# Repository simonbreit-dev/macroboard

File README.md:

# Makroboard

A macropad with twelve keys, two rotary encoders with push buttons, twelve
addressable RGB LEDs, and an RP2040. The 80 × 82 mm PCB uses four copper layers
and has a USB-C connector on its top edge.

This repository contains the editable electronics design. Firmware, an app, and
an enclosure are not included yet. The design **has not been tested as a physical
prototype**; USB communication, power supplies, and controls must be verified on
an assembled board.

## Getting started

1. Install KiCad 10, including its standard libraries. The design was edited with
   KiCad 10.0.7.
2. Open [`electronics/makroboard.kicad_pro`](electronics/makroboard.kicad_pro).
3. Read the [electronics documentation](electronics/README.md) and, before
   manufacturing, the [fabrication requirements](electronics/FABRICATION-NOTES.txt).

Project-specific symbols and footprints are included. The optional 3D models for
the USB-C connector and encoders are not included in the published project; all
pads, holes, and electrical connections are included.

## Files and exports

- `electronics/`: KiCad project, schematics, PCB, and library tables.
- `electronics/lib/footprints/`: local footprints used by the PCB.
- `LICENSE`, `LICENSES/`, `THIRD_PARTY.md`: license texts, attribution, and
  licensing notes.

Gerbers, drill files, assembly exports, previews, check results, and local agent
files are not versioned. Existing local files remain excluded by `.gitignore`.
Manufacturing files are exported from KiCad for the relevant revision; commands
are provided in the electronics documentation.

## Contributing

See [CONTRIBUTING.md](CONTRIBUTING.md). Keep hardware changes and documentation
consistent, and preserve the license notices.

## License and attribution

Copyright © 2026 Simon Breit. Original hardware contributions and the associated
project documentation are licensed under **CERN-OHL-P-2.0**; the full text is in
[LICENSE](LICENSE).

Third-party material retains its respective terms. The Raspberry Pi reference
design is licensed under MIT, KiCad library material under CC-BY-SA-4.0 with the
KiCad exception, and marbastlib key footprints under CERN-OHL-P-2.0.
The encoder footprints match those from
[ubiqueIoT/rotary-encoder-PEC11R](https://github.com/ubiqueIoT/rotary-encoder-PEC11R).
See [THIRD_PARTY.md](THIRD_PARTY.md) for further attribution and licensing notes.
CERN-OHL-P-2.0 does not grant additional rights to this third-party material.

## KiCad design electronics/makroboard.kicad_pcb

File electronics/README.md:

# Electronics

Revision **TOP-USB**, 2026-10-17: 80 × 82 mm, four copper layers, nominal finished
PCB thickness of 1.0 mm. Twelve keys form a 4×3 matrix with 19.05 mm key spacing;
the top row is 23 mm from the lower 3×3 block. Two encoders with push buttons sit
at the lower right, with USB-C on the top edge.

## Opening the project

Open `makroboard.kicad_pro` with KiCad 10. The files were edited with KiCad 10.0.7.
The KiCad standard libraries are required, along with the included
`Makroboard.kicad_sym` symbol library and the footprints under
`lib/footprints/Makroboard_PCB.pretty/`. The library tables use project-relative
paths.

`makroboard.kicad_sch` is the main schematic;
`RPI-RP2040-MINIMAL_R3-S1.kicad_sch` is the required controller subsheet, adapted
for Makroboard. Its filename identifies the original reference design. See
[THIRD_PARTY.md](../THIRD_PARTY.md) for attribution and licenses.

The optional external 3D models for USB-C and the encoders are not included.
Other components use embedded reference models and KiCad standard models.
Enclosure and control dimensions must be checked against manufacturer data;
no enclosure design is included.

## Assembly and fabrication

67 SMD/hybrid components are on Bottom; the two required 100 nF capacitors C20/C21
are on Top. C20/C21 use 0805 packages and can be hand-soldered after single-sided
factory assembly. One suitable part is Yageo CC0805KRX7R9BB104, LCSC C49678,
100 nF, 50 V, X7R, 10%.

R3 remains DNP. Keys, encoders, and the optional BOOT header J2 are assembled
separately. Test pads are not purchased components. The LEDs are reverse-mount
SK6812MINI-E devices on Bottom, shining through the PCB toward Top; confirm the
exact variant, pinout, and permitted brightness against the datasheet.

Include the [fabrication requirements](FABRICATION-NOTES.txt) with every
manufacturing order. In particular, the manufacturer must confirm 90 Ω ±10% USB
differential impedance for its actual four-layer stackup.

## Firmware interface

Firmware and an app are not included. The following assignments describe the
current design; they are not instructions for firmware that is already available.

| Signal | GPIO | RP2040 pin |
|---|---:|---:|
| MATRIX_COL_1 | 0 | 2 |
| MATRIX_COL_2 | 18 | 29 |
| MATRIX_COL_3 | 17 | 28 |
| MATRIX_ROW_1 | 3 | 5 |
| MATRIX_ROW_2 | 22 | 34 |
| MATRIX_ROW_3 | 11 | 14 |
| MATRIX_ROW_4 | 6 | 8 |
| LED_DATA | 8 | 11 |
| ENC_1_A | 29 | 41 |
| ENC_1_B | 28 | 40 |
| ENC_1_PUSH | 9 | 12 |
| ENC_2_A | 26 | 38 |
| ENC_2_B | 19 | 30 |
| ENC_2_PUSH | 24 | 36 |

The LED chain starts below SW3 at the upper right and follows a serpentine path
down the board:

| LED index (zero-based) | LED | Key | Matrix row | Matrix column |
|---:|---|---|---:|---:|
| 0 | D1 | SW3 | 1 | 3 |
| 1 | D2 | SW2 | 1 | 2 |
| 2 | D3 | SW1 | 1 | 1 |
| 3 | D4 | SW4 | 2 | 1 |
| 4 | D5 | SW5 | 2 | 2 |
| 5 | D6 | SW6 | 2 | 3 |
| 6 | D7 | SW9 | 3 | 3 |
| 7 | D8 | SW8 | 3 | 2 |
| 8 | D9 | SW7 | 3 | 1 |
| 9 | D10 | SW10 | 4 | 1 |
| 10 | D11 | SW11 | 4 | 2 |
| 11 | D12 | SW12 | 4 | 3 |

## Checks and exports

Run these commands from the repository root. On macOS, add
`/Applications/KiCad/KiCad.app/Contents/MacOS/` to `PATH` to use `kicad-cli`.
Outputs remain local and are excluded by `.gitignore`.

```sh
mkdir -p electronics/checks electronics/generated/gerbers
kicad-cli sch erc --format json --severity-all --exit-code-violations \
  -o electronics/checks/erc.json electronics/makroboard.kicad_sch
kicad-cli pcb drc --format json --schematic-parity --refill-zones \
  --exit-code-violations -o electronics/checks/drc.json \
  electronics/makroboard.kicad_pcb
kicad-cli pcb export gerbers \
  --layers F.Cu,In1.Cu,In2.Cu,B.Cu,F.Mask,B.Mask,F.Silkscreen,B.Silkscreen,F.Paste,B.Paste,Edge.Cuts \
  --use-drill-file-origin --subtract-soldermask --check-zones \
  -o electronics/generated/gerbers/ electronics/makroboard.kicad_pcb
kicad-cli pcb export drill --format excellon --drill-origin plot \
  --excellon-separate-th --excellon-oval-format route \
  -o electronics/generated/gerbers/ electronics/makroboard.kicad_pcb
```

Always generate Gerbers, drill files, and any BOM/placement files from the same
project revision, and inspect them together in KiCad/Gerber Viewer. For new
assembly exports, explicitly define which parts are factory-assembled and which
are hand-soldered. The assembler must verify machine rotation offsets against
the pin-1 markings. Old local exports are not an approved manufacturing package.

The project intentionally disables some ERC/DRC rules, such as missing
courtyards. Interpret a successful check within that configuration; it does not
verify enclosure fit or hardware functionality.

## First power-up

The design **has not been tested as a physical prototype**. After completing
assembly, including C20/C21, check for solder bridges, monitor current draw, and
verify the +3V3 and +1V1 supplies.

To enter the ROM USB bootloader, connect J2 pin 1 to GND, briefly pull RUN at TP3
to GND and release it, then release BOOT. `RPI-RP2` should appear. Alternatively,
use TP1 SWCLK, TP2 SWDIO, TP3 RUN, TP4 GND, and TP5 as the 3.3 V reference for SWD.
Start LED testing at low brightness. Power-up, flashing, USB communication, and
key/encoder/LED operation must be verified on an assembled board with suitable
firmware.

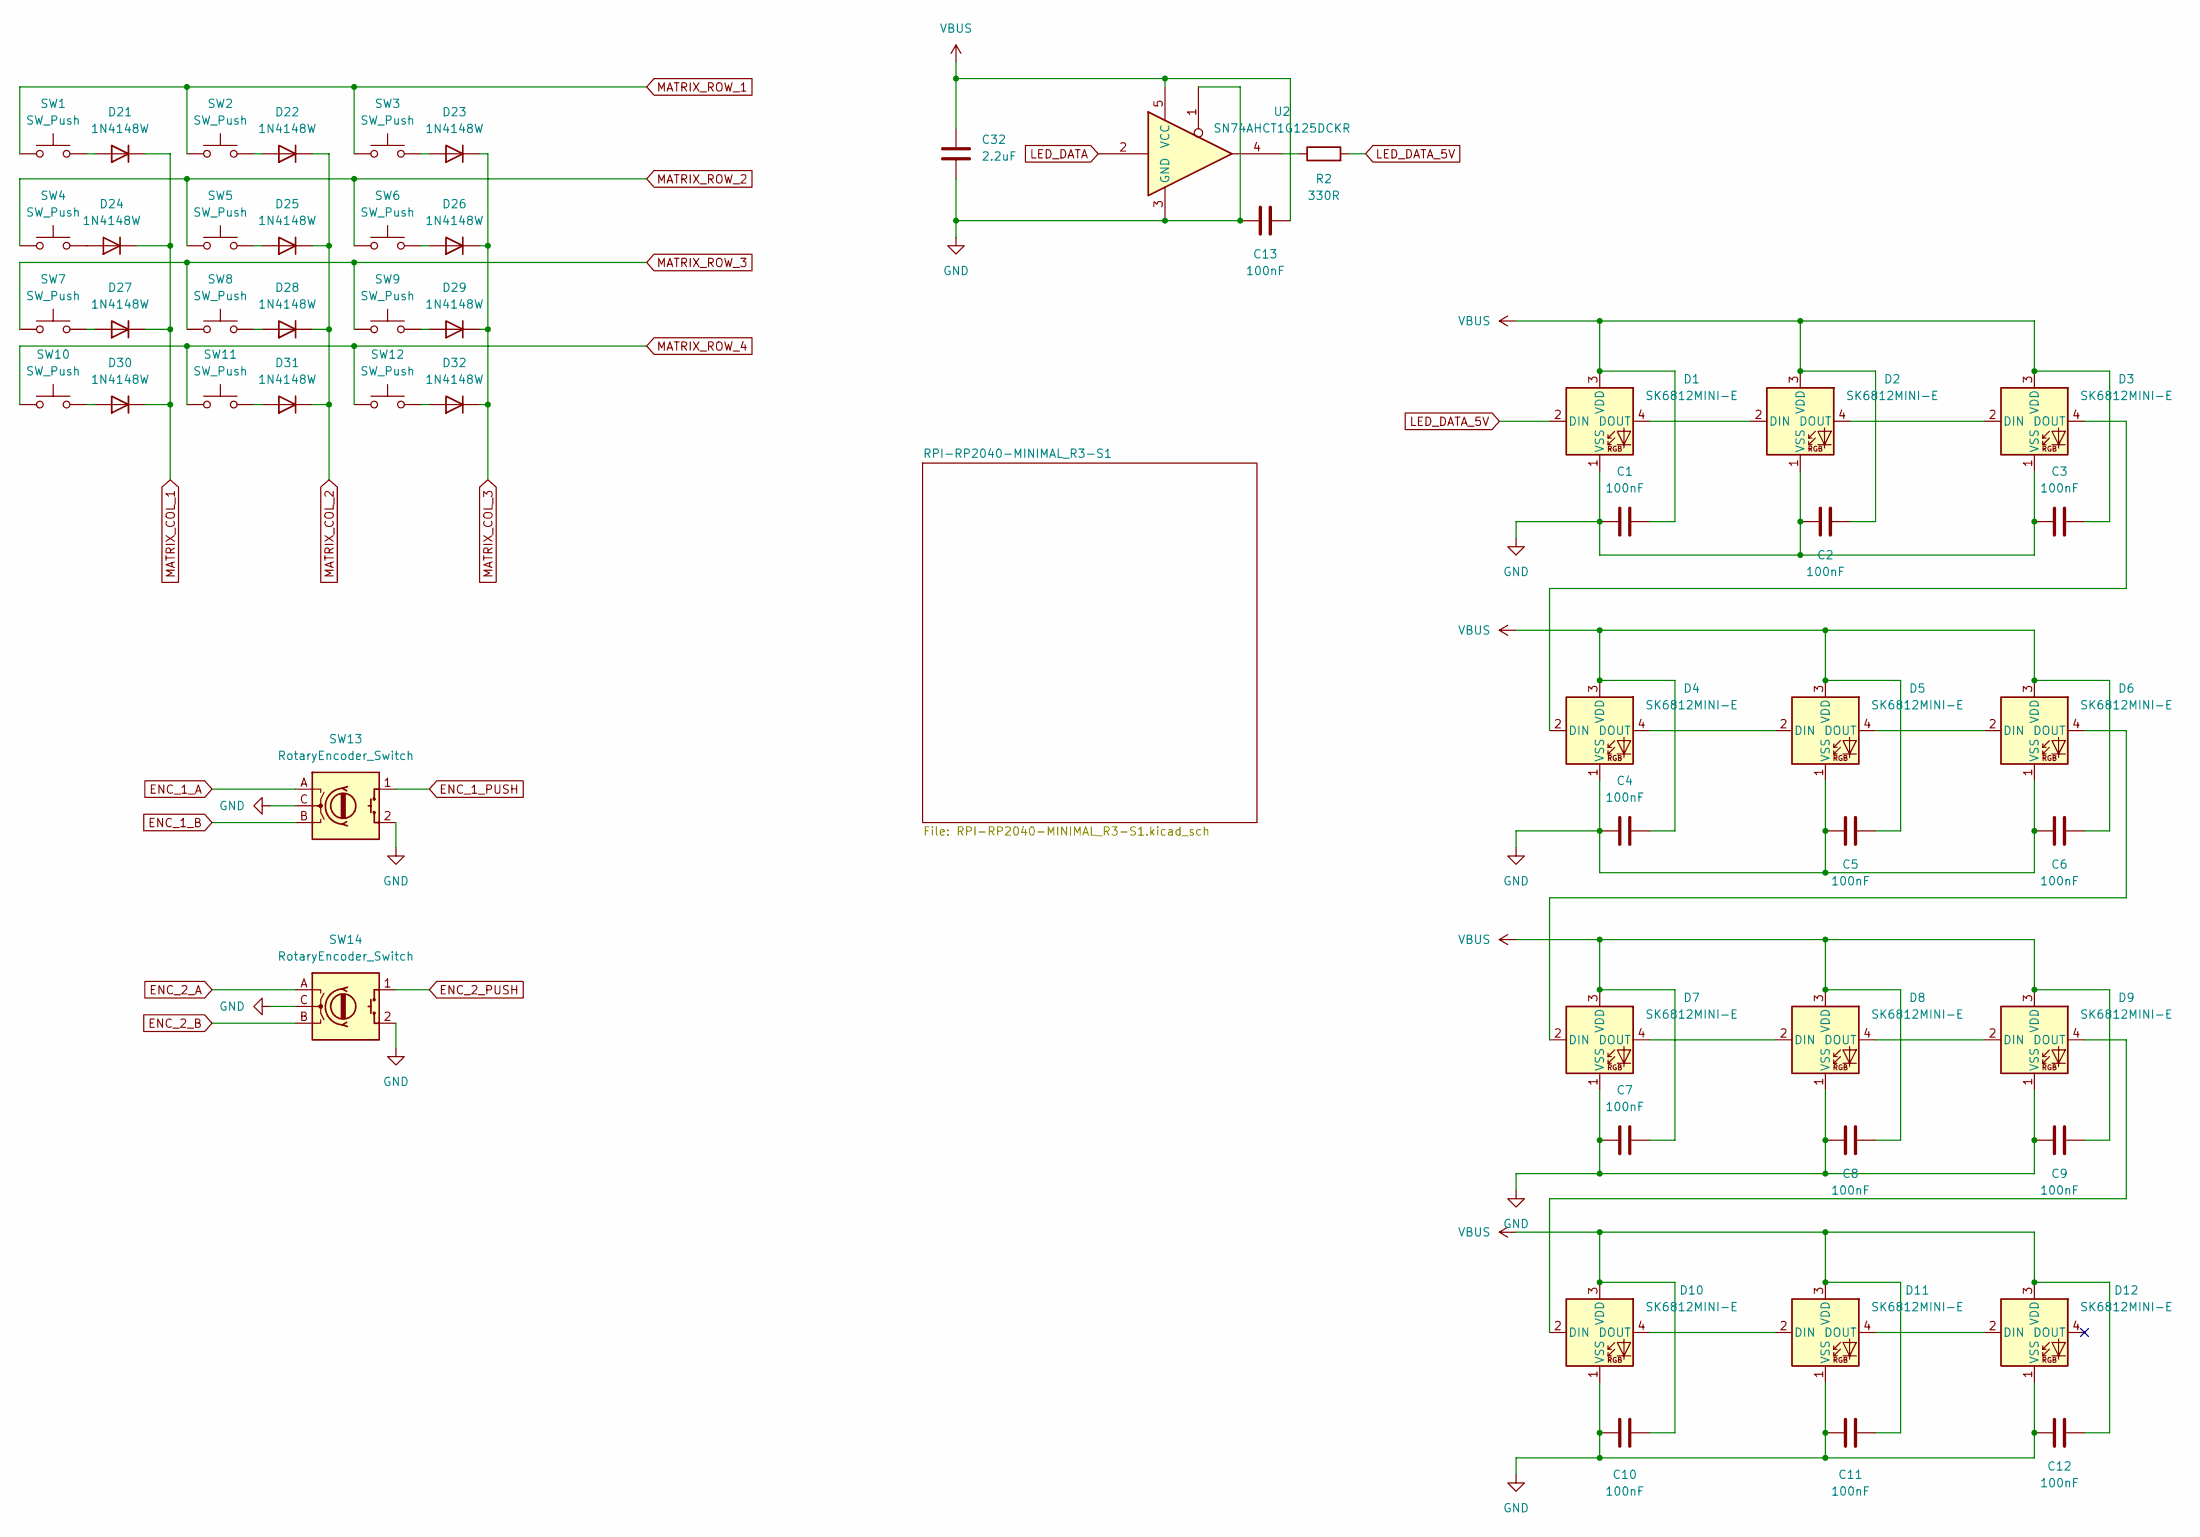
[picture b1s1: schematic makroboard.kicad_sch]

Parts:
C1: 100nF; C1_C_0805_2012Metric; manufacturer_pn CC0805KRX7R9BB104; LCSC C49678
C2: 100nF; C2_C_0805_2012Metric; manufacturer_pn CC0805KRX7R9BB104; LCSC C49678
C3: 100nF; C3_C_0805_2012Metric; manufacturer_pn CC0805KRX7R9BB104; LCSC C49678
C4: 100nF; C4_C_0805_2012Metric; manufacturer_pn CC0805KRX7R9BB104; LCSC C49678
C5: 100nF; C5_C_0805_2012Metric; manufacturer_pn CC0805KRX7R9BB104; LCSC C49678
C6: 100nF; C6_C_0805_2012Metric; manufacturer_pn CC0805KRX7R9BB104; LCSC C49678
C7: 100nF; C7_C_0805_2012Metric; manufacturer_pn CC0805KRX7R9BB104; LCSC C49678
C8: 100nF; C8_C_0805_2012Metric; manufacturer_pn CC0805KRX7R9BB104; LCSC C49678
C9: 100nF; C9_C_0805_2012Metric; manufacturer_pn CC0805KRX7R9BB104; LCSC C49678
C10: 100nF; C10_C_0805_2012Metric; manufacturer_pn CC0805KRX7R9BB104; LCSC C49678
C11: 100nF; C11_C_0805_2012Metric; manufacturer_pn CC0805KRX7R9BB104; LCSC C49678
C12: 100nF; C12_C_0805_2012Metric; manufacturer_pn CC0805KRX7R9BB104; LCSC C49678
C13: 100nF; C13_C_0805_2012Metric; manufacturer_pn CC0805KRX7R9BB104; LCSC C49678
C32: 2.2uF; C32_C_0805_2012Metric; manufacturer_pn CL21B225KOFNNNE; LCSC C28234
D1: SK6812MINI-E; D1_LED_SK6812MINI-E_3.2x2.8mm_P1.5mm_ReverseMount; manufacturer_pn SK6812MINI-E; LCSC C5149201
D2: SK6812MINI-E; D2_LED_SK6812MINI-E_3.2x2.8mm_P1.5mm_ReverseMount; manufacturer_pn SK6812MINI-E; LCSC C5149201
D3: SK6812MINI-E; D3_LED_SK6812MINI-E_3.2x2.8mm_P1.5mm_ReverseMount; manufacturer_pn SK6812MINI-E; LCSC C5149201
D4: SK6812MINI-E; D4_LED_SK6812MINI-E_3.2x2.8mm_P1.5mm_ReverseMount; manufacturer_pn SK6812MINI-E; LCSC C5149201
D5: SK6812MINI-E; D5_LED_SK6812MINI-E_3.2x2.8mm_P1.5mm_ReverseMount; manufacturer_pn SK6812MINI-E; LCSC C5149201
D6: SK6812MINI-E; D6_LED_SK6812MINI-E_3.2x2.8mm_P1.5mm_ReverseMount; manufacturer_pn SK6812MINI-E; LCSC C5149201
D7: SK6812MINI-E; D7_LED_SK6812MINI-E_3.2x2.8mm_P1.5mm_ReverseMount; manufacturer_pn SK6812MINI-E; LCSC C5149201
D8: SK6812MINI-E; D8_LED_SK6812MINI-E_3.2x2.8mm_P1.5mm_ReverseMount; manufacturer_pn SK6812MINI-E; LCSC C5149201
D9: SK6812MINI-E; D9_LED_SK6812MINI-E_3.2x2.8mm_P1.5mm_ReverseMount; manufacturer_pn SK6812MINI-E; LCSC C5149201
D10: SK6812MINI-E; D10_LED_SK6812MINI-E_3.2x2.8mm_P1.5mm_ReverseMount; manufacturer_pn SK6812MINI-E; LCSC C5149201
D11: SK6812MINI-E; D11_LED_SK6812MINI-E_3.2x2.8mm_P1.5mm_ReverseMount; manufacturer_pn SK6812MINI-E; LCSC C5149201
D12: SK6812MINI-E; D12_LED_SK6812MINI-E_3.2x2.8mm_P1.5mm_ReverseMount; manufacturer_pn SK6812MINI-E; LCSC C5149201
D21: 1N4148W; D21_D_SOD-123; manufacturer_pn 1N4148W; LCSC C81598
D22: 1N4148W; D22_D_SOD-123; manufacturer_pn 1N4148W; LCSC C81598
D23: 1N4148W; D23_D_SOD-123; manufacturer_pn 1N4148W; LCSC C81598
D24: 1N4148W; D24_D_SOD-123; manufacturer_pn 1N4148W; LCSC C81598
D25: 1N4148W; D25_D_SOD-123; manufacturer_pn 1N4148W; LCSC C81598
D26: 1N4148W; D26_D_SOD-123; manufacturer_pn 1N4148W; LCSC C81598
D27: 1N4148W; D27_D_SOD-123; manufacturer_pn 1N4148W; LCSC C81598
D28: 1N4148W; D28_D_SOD-123; manufacturer_pn 1N4148W; LCSC C81598
D29: 1N4148W; D29_D_SOD-123; manufacturer_pn 1N4148W; LCSC C81598
D30: 1N4148W; D30_D_SOD-123; manufacturer_pn 1N4148W; LCSC C81598
D31: 1N4148W; D31_D_SOD-123; manufacturer_pn 1N4148W; LCSC C81598
D32: 1N4148W; D32_D_SOD-123; manufacturer_pn 1N4148W; LCSC C81598
R2: 330R; R2_R_0805_2012Metric; manufacturer_pn 0805W8F3300T5E; LCSC C17630
SW1: SW_Push; SW1_SW_choc_v2_1u
SW2: SW_Push; SW2_SW_choc_v2_1u
SW3: SW_Push; SW3_SW_choc_v2_1u
SW4: SW_Push; SW4_SW_choc_v2_1u
SW5: SW_Push; SW5_SW_choc_v2_1u
SW6: SW_Push; SW6_SW_choc_v2_1u
SW7: SW_Push; SW7_SW_choc_v2_1u
SW8: SW_Push; SW8_SW_choc_v2_1u
SW9: SW_Push; SW9_SW_choc_v2_1u
SW10: SW_Push; SW10_SW_choc_v2_1u
SW11: SW_Push; SW11_SW_choc_v2_1u
SW12: SW_Push; SW12_SW_choc_v2_1u
SW13: RotaryEncoder_Switch; SW13_Bourns-PEC11R-4220F-S0024-0-0-0
SW14: RotaryEncoder_Switch; SW14_Bourns-PEC11R-4220F-S0024-0-0-0
U2: SN74AHCT1G125DCKR; U2_SOT-353_SC-70-5; manufacturer_pn SN74AHCT1G125DCKR; LCSC C350557

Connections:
ENC_1_A: SW13.A; also elsewhere on the board
ENC_1_B: SW13.B; also elsewhere on the board
ENC_1_PUSH: SW13.1 (S1); also elsewhere on the board
ENC_2_A: SW14.A; also elsewhere on the board
ENC_2_B: SW14.B; also elsewhere on the board
ENC_2_PUSH: SW14.1 (S1); also elsewhere on the board
GND: C1.2, C2.2, C3.2, C4.2, C5.2, C6.2, C7.2, C8.2, C9.2, C10.2, C11.2, C12.2, C13.2, C32.2, D1.1 (VSS), D2.1 (VSS), D3.1 (VSS), D4.1 (VSS), D5.1 (VSS), D6.1 (VSS), D7.1 (VSS), D8.1 (VSS), D9.1 (VSS), D10.1 (VSS), D11.1 (VSS), D12.1 (VSS), SW13.2 (S2), SW13.C, SW14.2 (S2), SW14.C, U2.1, U2.3 (GND); also elsewhere on the board
LED_DATA: U2.2; also elsewhere on the board
LED_DATA_5V: D1.2 (DIN), R2.2
MATRIX_COL_1: D21.1 (K), D24.1 (K), D27.1 (K), D30.1 (K); also elsewhere on the board
MATRIX_COL_2: D22.1 (K), D25.1 (K), D28.1 (K), D31.1 (K); also elsewhere on the board
MATRIX_COL_3: D23.1 (K), D26.1 (K), D29.1 (K), D32.1 (K); also elsewhere on the board
MATRIX_ROW_1: SW1.1, SW2.1, SW3.1; also elsewhere on the board
MATRIX_ROW_2: SW4.1, SW5.1, SW6.1; also elsewhere on the board
MATRIX_ROW_3: SW7.1, SW8.1, SW9.1; also elsewhere on the board
MATRIX_ROW_4: SW10.1, SW11.1, SW12.1; also elsewhere on the board
unnamed: D1.4 (DOUT), D2.2 (DIN)
unnamed: D2.4 (DOUT), D3.2 (DIN)
unnamed: D3.4 (DOUT), D4.2 (DIN)
unnamed: D4.4 (DOUT), D5.2 (DIN)
unnamed: D5.4 (DOUT), D6.2 (DIN)
unnamed: D6.4 (DOUT), D7.2 (DIN)
unnamed: D7.4 (DOUT), D8.2 (DIN)
unnamed: D8.4 (DOUT), D9.2 (DIN)
unnamed: D9.4 (DOUT), D10.2 (DIN)
unnamed: D10.4 (DOUT), D11.2 (DIN)
unnamed: D11.4 (DOUT), D12.2 (DIN)
unnamed: D21.2 (A), SW1.2
unnamed: D22.2 (A), SW2.2
unnamed: D23.2 (A), SW3.2
unnamed: D24.2 (A), SW4.2
unnamed: D25.2 (A), SW5.2
unnamed: D26.2 (A), SW6.2
unnamed: D27.2 (A), SW7.2
unnamed: D28.2 (A), SW8.2
unnamed: D29.2 (A), SW9.2
unnamed: D30.2 (A), SW10.2
unnamed: D31.2 (A), SW11.2
unnamed: D32.2 (A), SW12.2
unnamed: R2.1, U2.4
VBUS: C1.1, C2.1, C3.1, C4.1, C5.1, C6.1, C7.1, C8.1, C9.1, C10.1, C11.1, C12.1, C13.1, C32.1, D1.3 (VDD), D2.3 (VDD), D3.3 (VDD), D4.3 (VDD), D5.3 (VDD), D6.3 (VDD), D7.3 (VDD), D8.3 (VDD), D9.3 (VDD), D10.3 (VDD), D11.3 (VDD), D12.3 (VDD), U2.5 (VCC); also elsewhere on the board

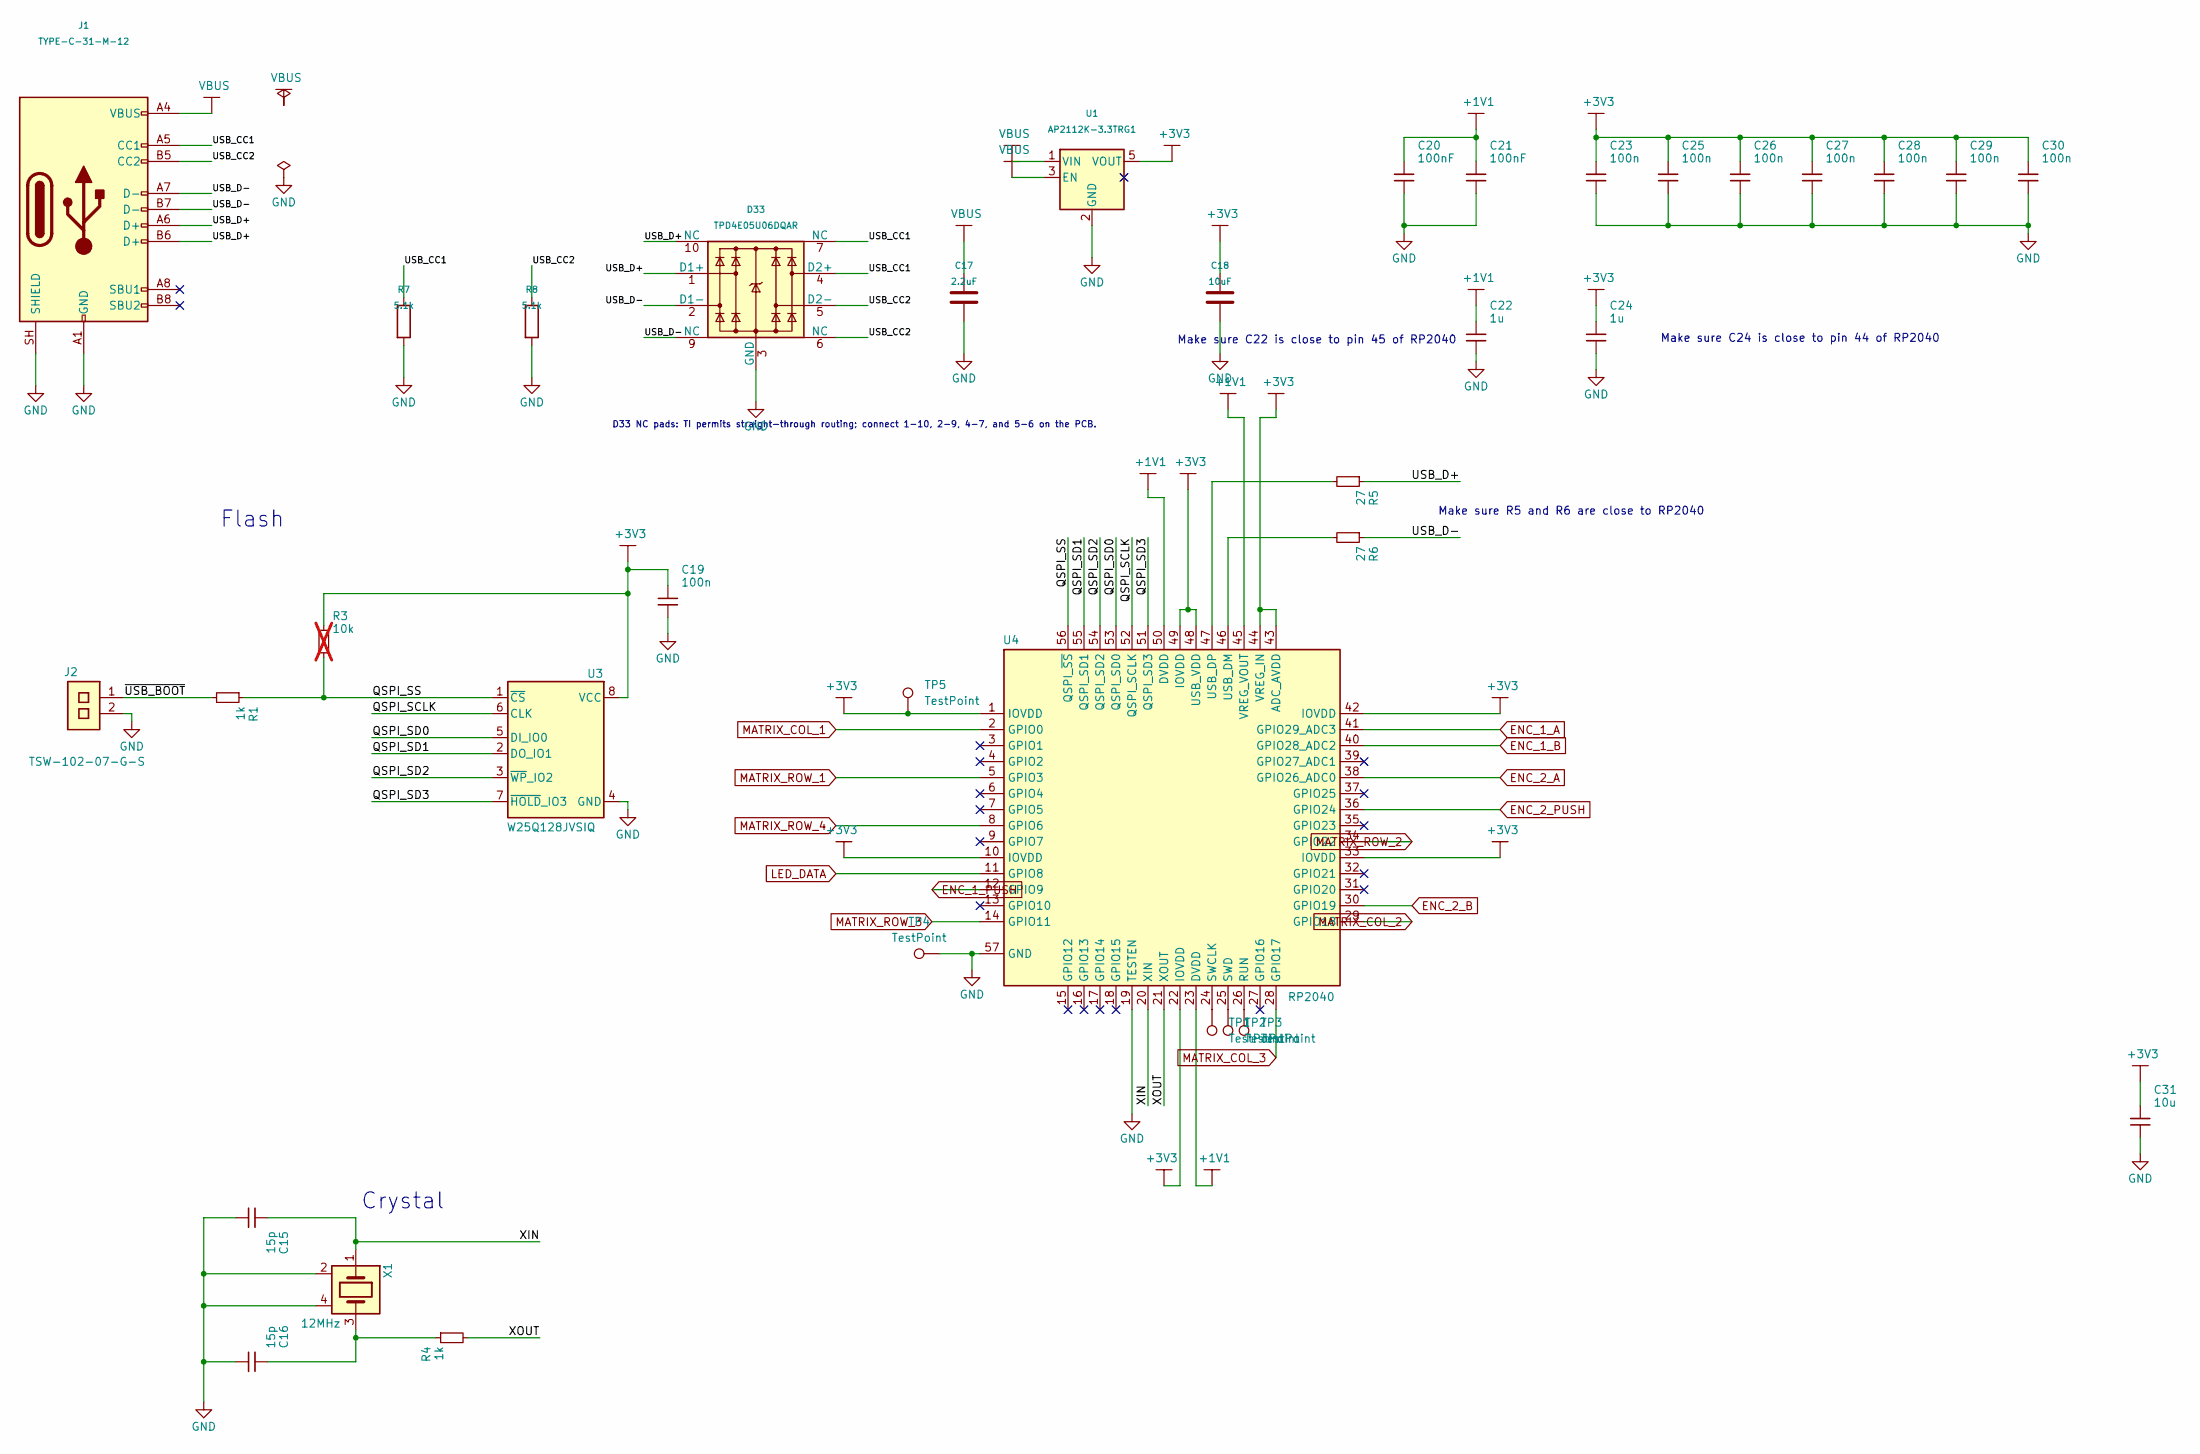
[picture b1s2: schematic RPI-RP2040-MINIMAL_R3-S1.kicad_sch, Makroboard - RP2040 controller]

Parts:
C15: 15p; C15_generic_capc1005x50; manufacturer_pn 0402CG150J500NT; LCSC C1548
C16: 15p; C16_generic_capc1005x50; manufacturer_pn 0402CG150J500NT; LCSC C1548
C17: 2.2uF; C17_generic_capc2012x125; manufacturer_pn CL21B225KOFNNNE; LCSC C28234
C18: 10uF; C18_generic_capc2012x125; manufacturer_pn CL21A106KAYNNNE; LCSC C15850
C19: 100n; C19_generic_capc1005x50; manufacturer_pn CL05B104KO5NNNC; LCSC C1525
C20: 100nF; C20_C_0805_2012Metric; manufacturer_pn CC0805KRX7R9BB104; LCSC C49678
C21: 100nF; C21_C_0805_2012Metric; manufacturer_pn CC0805KRX7R9BB104; LCSC C49678
C22: 1u; C22_generic_capc1005x50; manufacturer_pn CL05A105KA5NQNC; LCSC C52923
C23: 100n; C23_generic_capc1005x50; manufacturer_pn CL05B104KO5NNNC; LCSC C1525
C24: 1u; C24_generic_capc1005x50; manufacturer_pn CL05A105KA5NQNC; LCSC C52923
C25: 100n; C25_generic_capc1005x50; manufacturer_pn CL05B104KO5NNNC; LCSC C1525
C26: 100n; C26_generic_capc1005x50; manufacturer_pn CL05B104KO5NNNC; LCSC C1525
C27: 100n; C27_generic_capc1005x50; manufacturer_pn CL05B104KO5NNNC; LCSC C1525
C28: 100n; C28_generic_capc1005x50; manufacturer_pn CL05B104KO5NNNC; LCSC C1525
C29: 100n; C29_generic_capc1005x50; manufacturer_pn CL05B104KO5NNNC; LCSC C1525
C30: 100n; C30_generic_capc1005x50; manufacturer_pn CL05B104KO5NNNC; LCSC C1525
C31: 10u; C31_generic_capc2012x125; manufacturer_pn CL21A106KAYNNNE; LCSC C15850
D33: TPD4E05U06DQAR; D33_USON-10_2.5x1.0mm_P0.5mm; manufacturer_pn TPD4E05U06DQAR; LCSC C138714
J1: TYPE-C-31-M-12; J1_USB_C_Receptacle_HRO_TYPE-C-31-M-12; manufacturer_pn TYPE-C-31-M-12; LCSC C165948
J2: TSW-102-07-G-S; J2_samtec_tsw-102-07-g-s; part_uid RP-01JV5X-LY21H5
R1: 1k; R1_generic_resc1005x35; manufacturer_pn 0402WGF1001TCE; LCSC C11702
R3: 10k; R3_generic_resc1005x35; manufacturer_pn 0402WGF1002TCE; LCSC C25744; not fitted
R4: 1k; R4_generic_resc1005x35; manufacturer_pn 0402WGF1001TCE; LCSC C11702
R5: 27; R5_generic_resc1005x35; manufacturer_pn 0402WGF270JTCE; LCSC C25100
R6: 27; R6_generic_resc1005x35; manufacturer_pn 0402WGF270JTCE; LCSC C25100
R7: 5.1k; R7_R_0603_1608Metric; manufacturer_pn 0603WAF5101T5E; LCSC C23186
R8: 5.1k; R8_R_0603_1608Metric; manufacturer_pn 0603WAF5101T5E; LCSC C23186
TP1: TestPoint; TP1_TestPoint_Pad_D1.5mm
TP2: TestPoint; TP2_TestPoint_Pad_D1.5mm
TP3: TestPoint; TP3_TestPoint_Pad_D1.5mm
TP4: TestPoint; TP4_TestPoint_Pad_D1.5mm
TP5: TestPoint; TP5_TestPoint_Pad_D1.5mm
U1: AP2112K-3.3TRG1; U1_SOT-23-5; manufacturer_pn AP2112K-3.3TRG1; LCSC C51118
U3: W25Q128JVSIQ; U3_generic_soic127p790x195-8; manufacturer_pn W25Q128JVSIQ; LCSC C97521
U4: RP2040; U4_rpi_rp2040_vias; manufacturer_pn RP2040; LCSC C2040
X1: 12MHz; X1_generic_xtalcc320x250x80-4; manufacturer_pn ABM8-272-T3; LCSC C20625731

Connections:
+1V1: C20.1, C21.1, C22.1, U4.23 (DVDD), U4.45 (VREG_VOUT), U4.50 (DVDD)
+3V3: C18.1, C19.1, C23.1, C24.1, C25.1, C26.1, C27.1, C28.1, C29.1, C30.1, C31.1, R3.1, TP5.1 (1_1), U1.5 (VOUT), U3.8 (VCC), U4.1 (IOVDD), U4.10 (IOVDD), U4.22 (IOVDD), U4.33 (IOVDD), U4.42 (IOVDD), U4.43 (ADC_AVDD), U4.44 (VREG_IN), U4.48 (USB_VDD), U4.49 (IOVDD)
/RPI-RP2040-MINIMAL_R3-S1/QSPI_SCLK: U3.6 (CLK), U4.52 (QSPI_SCLK)
/RPI-RP2040-MINIMAL_R3-S1/QSPI_SD0: U3.5 (DI_IO0), U4.53 (QSPI_SD0)
/RPI-RP2040-MINIMAL_R3-S1/QSPI_SD1: U3.2 (DO_IO1), U4.55 (QSPI_SD1)
/RPI-RP2040-MINIMAL_R3-S1/QSPI_SD2: U3.3 (~WP_IO2), U4.54 (QSPI_SD2)
/RPI-RP2040-MINIMAL_R3-S1/QSPI_SD3: U3.7 (~HOLD_IO3), U4.51 (QSPI_SD3)
/RPI-RP2040-MINIMAL_R3-S1/QSPI_SS: R1.1, R3.2, U3.1 (~CS), U4.56 (QSPI_~SS)
/RPI-RP2040-MINIMAL_R3-S1/USB_CC1: D33.4 (D2+), D33.7 (NC), J1.A5 (CC1), R7.1
/RPI-RP2040-MINIMAL_R3-S1/USB_CC2: D33.5 (D2-), D33.6 (NC), J1.B5 (CC2), R8.1
/RPI-RP2040-MINIMAL_R3-S1/USB_D+: D33.1 (D1+), D33.10 (NC), J1.A6 (D+), J1.B6 (D+), R5.1
/RPI-RP2040-MINIMAL_R3-S1/USB_D-: D33.2 (D1-), D33.9 (NC), J1.A7 (D-), J1.B7 (D-), R6.1
/RPI-RP2040-MINIMAL_R3-S1/XIN: C15.1, U4.20 (XIN), X1.1
/RPI-RP2040-MINIMAL_R3-S1/XOUT: R4.2, U4.21 (XOUT)
/RPI-RP2040-MINIMAL_R3-S1/~USB_BOOT: J2.1, R1.2
ENC_1_A: U4.41 (GPIO29_ADC3); also elsewhere on the board
ENC_1_B: U4.40 (GPIO28_ADC2); also elsewhere on the board
ENC_1_PUSH: U4.12 (GPIO9); also elsewhere on the board
ENC_2_A: U4.38 (GPIO26_ADC0); also elsewhere on the board
ENC_2_B: U4.30 (GPIO19); also elsewhere on the board
ENC_2_PUSH: U4.36 (GPIO24); also elsewhere on the board
GND: C15.2, C16.2, C17.2, C18.2, C19.2, C20.2, C21.2, C22.2, C23.2, C24.2, C25.2, C26.2, C27.2, C28.2, C29.2, C30.2, C31.2, D33.3 (GND), D33.8 (GND), J1.A1 (GND), J1.A12 (GND), J1.B1 (GND), J1.B12 (GND), J1.SH (SHIELD), J2.2, R7.2, R8.2, TP4.1 (1_1), U1.2 (GND), U3.4 (GND), U4.19 (TESTEN), U4.57 (GND), X1.2, X1.4; also elsewhere on the board
LED_DATA: U4.11 (GPIO8); also elsewhere on the board
MATRIX_COL_1: U4.2 (GPIO0); also elsewhere on the board
MATRIX_COL_2: U4.29 (GPIO18); also elsewhere on the board
MATRIX_COL_3: U4.28 (GPIO17); also elsewhere on the board
MATRIX_ROW_1: U4.5 (GPIO3); also elsewhere on the board
MATRIX_ROW_2: U4.34 (GPIO22); also elsewhere on the board
MATRIX_ROW_3: U4.14 (GPIO11); also elsewhere on the board
MATRIX_ROW_4: U4.8 (GPIO6); also elsewhere on the board
unnamed: C16.1, R4.1, X1.3
unnamed: TP3.1 (1_1), U4.26 (RUN)
unnamed: TP1.1 (1_1), U4.24 (SWCLK)
unnamed: TP2.1 (1_1), U4.25 (SWD)
unnamed: R6.2, U4.46 (USB_DM)
unnamed: R5.2, U4.47 (USB_DP)
VBUS: C17.1, J1.A4 (VBUS), J1.A9 (VBUS), J1.B4 (VBUS), J1.B9 (VBUS), U1.1 (VIN), U1.3 (EN); also elsewhere on the board

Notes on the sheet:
Crystal
Make sure C22 is close to pin 45 of RP2040
Make sure C24 is close to pin 44 of RP2040
Make sure R5 and R6 are close to RP2040
Flash
D33 NC pads: TI permits straight-through routing; connect 1-10, 2-9, 4-7, and 5-6 on the PCB.

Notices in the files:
electronics/RPI-RP2040-MINIMAL_R3-S1.kicad_sch:
Makroboard modifications: Copyright 2026 Simon Breit
CERN-OHL-P-2.0; see ../THIRD_PARTY.md for third-party notices
